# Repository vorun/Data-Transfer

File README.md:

# Data-Transfer
Communication Between 2 MSP430 Microcontroller Via Bluetooth

-When you press the button at the master msp430, data which is 0x11 gets sent to slave 
msp430 via bluetooth using uart. As long as the data coming from the master msp430 is equal to '2'
slave msp430's led lights up.

-In order to transmit data with bluetooth module you need to configure your bluetooth modules to 
master/slave.

-Slave circuit can be configured to control a device with the master circuit or with any device with bluetooth 
capability.  

-Pin connections and circiut designs can be found at the "MSP430 Bluetooth Comm PCB" folder.

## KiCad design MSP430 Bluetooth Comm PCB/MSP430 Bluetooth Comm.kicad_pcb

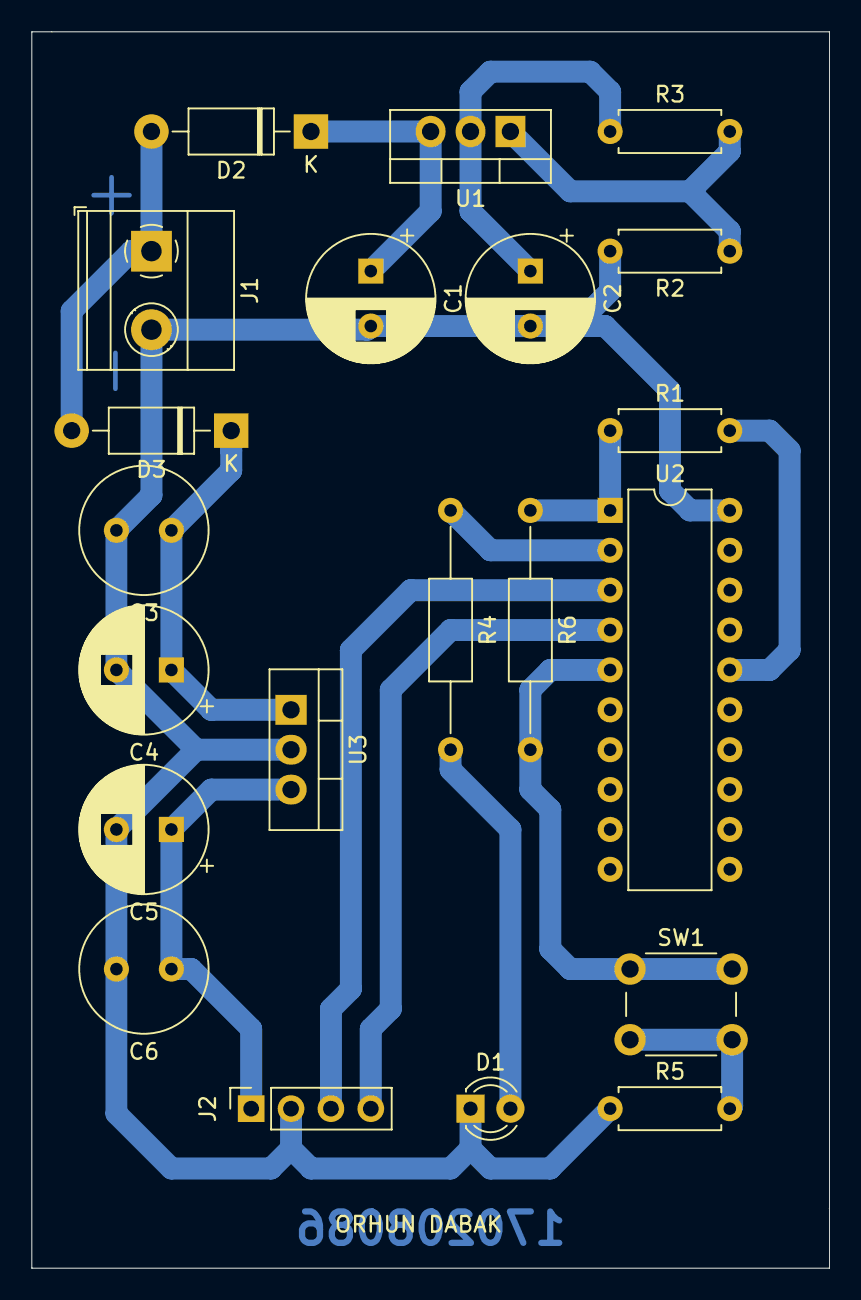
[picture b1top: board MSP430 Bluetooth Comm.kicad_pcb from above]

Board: 2 copper layers, 50.8 x 78.7 mm, 21 parts (0 on the bottom side), 15 nets.

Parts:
C1, C4: 220uF; CP_Radial_D8.0mm_P3.50mm
C2: 10uF; CP_Radial_D8.0mm_P3.50mm
C3, C6: 100nF; C_Radial_D8.0mm_H7.0mm_P3.50mm
C5: 1uF; CP_Radial_D8.0mm_P3.50mm
D1: LED; LED_D3.0mm
D2, D3: 1N4001; D_DO-41_SOD81_P10.16mm_Horizontal
J1: 9V; TerminalBlock_Phoenix_MKDS-1,5-2_1x02_P5.00mm_Horizontal
J2: HC05; PinSocket_1x04_P2.54mm_Vertical
R1: 47k; R_Axial_DIN0207_L6.3mm_D2.5mm_P7.62mm_Horizontal
R2: 390; R_Axial_DIN0207_L6.3mm_D2.5mm_P7.62mm_Horizontal
R3: 240; R_Axial_DIN0207_L6.3mm_D2.5mm_P7.62mm_Horizontal
R4: 220; R_Axial_DIN0207_L6.3mm_D2.5mm_P15.24mm_Horizontal
R5: 220; R_Axial_DIN0207_L6.3mm_D2.5mm_P7.62mm_Horizontal
R6: 10k; R_Axial_DIN0207_L6.3mm_D2.5mm_P15.24mm_Horizontal
SW1: SW_DIP_x01; SW_PUSH_6mm_H4.3mm
U1: LM317_TO-220; TO-220-3_Vertical
U2: MSP430G2553IN20; DIP-20_W7.62mm
U3: LM7805_TO220; TO-220-3_Vertical

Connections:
GND: C1.2, C2.2, C3.2, C4.2, C5.2, C6.2, D1.1, J1.2, J2.2, R2.2, R5.1, U2.20, U3.2
unnamed: C1.1, D2.1, U1.3
unnamed: C2.1, R3.1, U1.2
unnamed: C3.1, C4.1, D3.1, U3.1
unnamed: C5.1, C6.1, J2.1, U3.3
unnamed: D1.2, R4.2
unnamed: D2.2, D3.2, J1.1
unnamed: J2.3, U2.3
unnamed: J2.4, U2.4
unnamed: R1.1, R6.1, U2.1
unnamed: R1.2, U2.16
unnamed: R2.1, R3.2, U1.1
unnamed: R4.1, U2.2
unnamed: R5.2, SW1.2
unnamed: R6.2, SW1.1, U2.5
